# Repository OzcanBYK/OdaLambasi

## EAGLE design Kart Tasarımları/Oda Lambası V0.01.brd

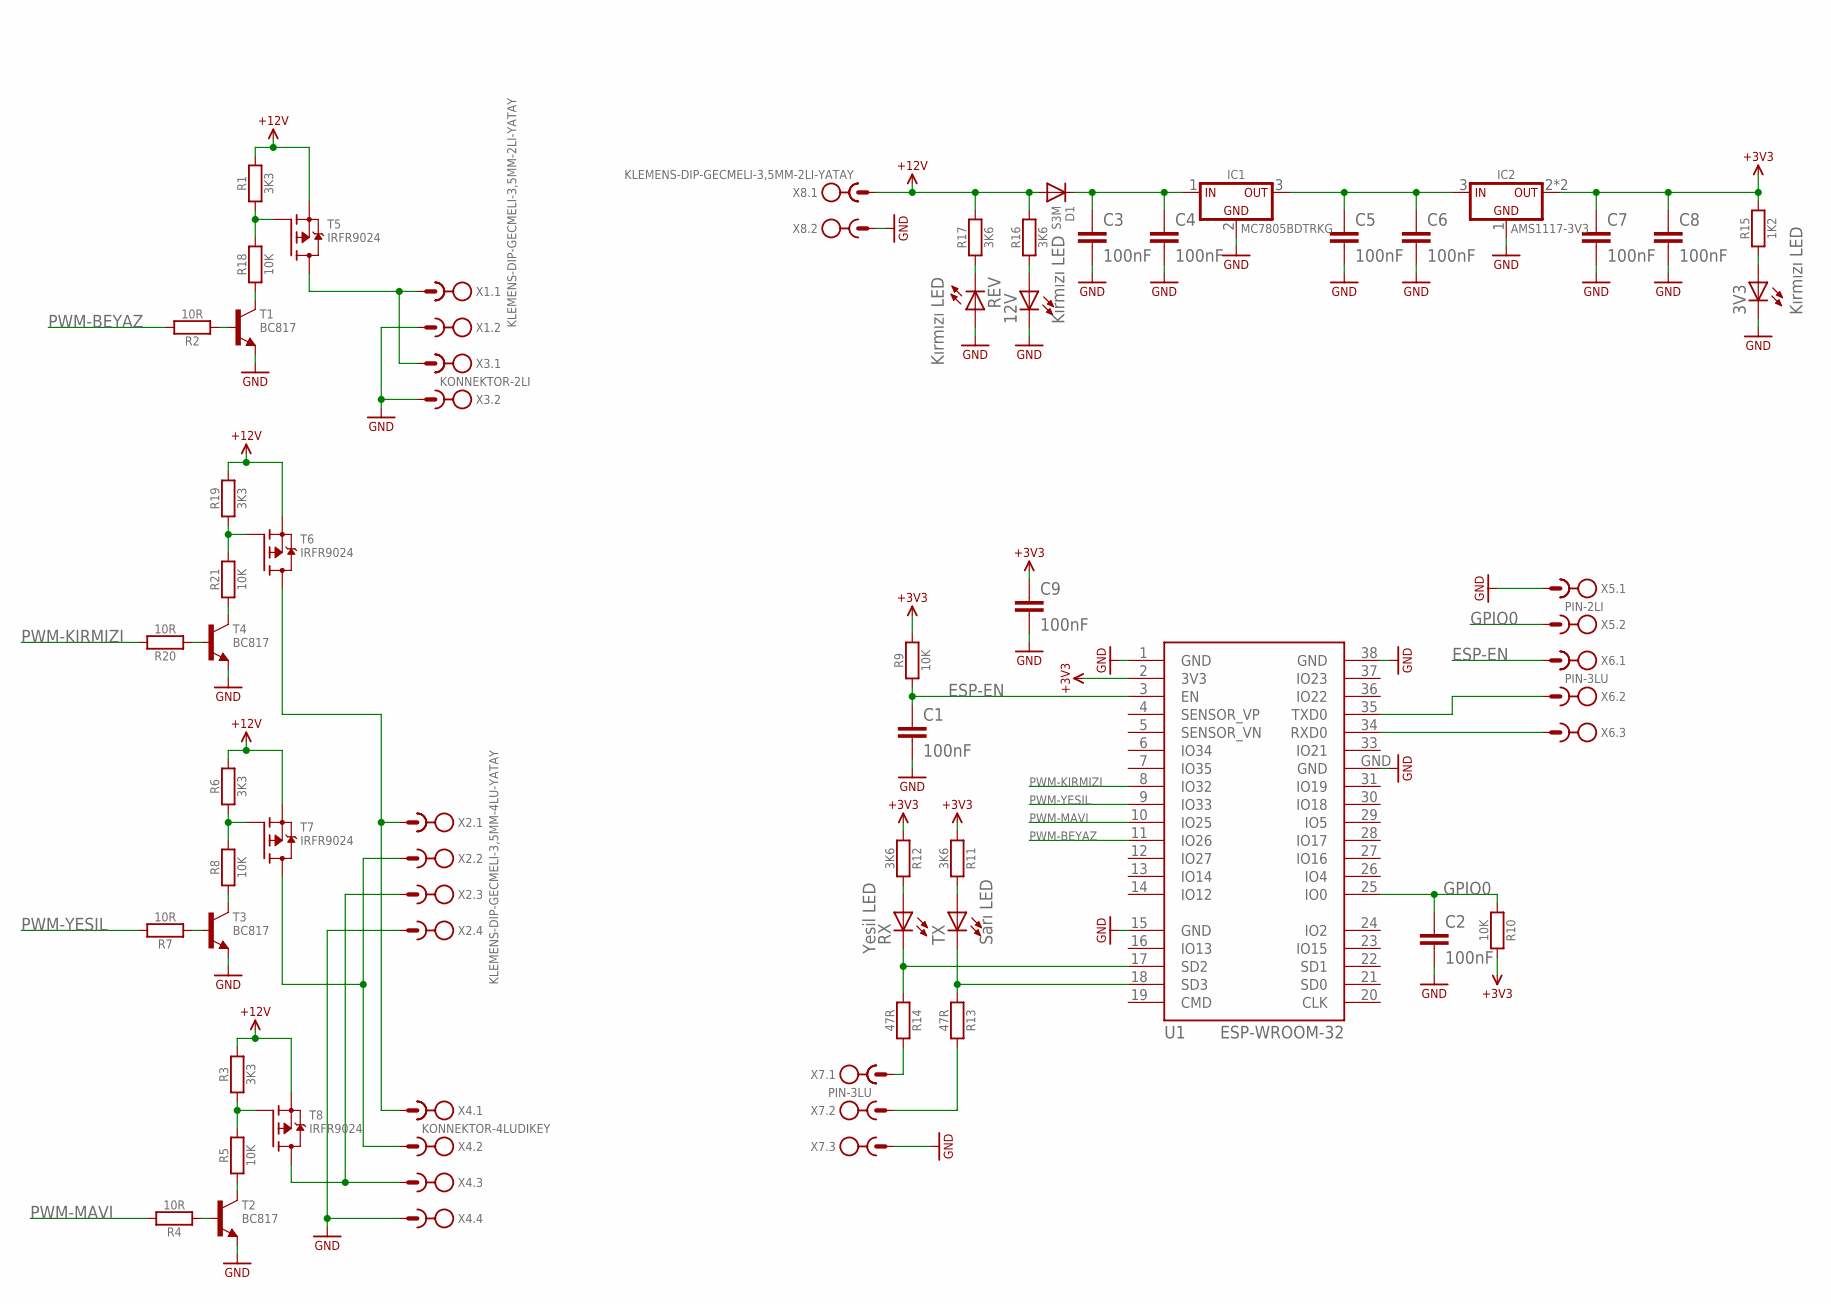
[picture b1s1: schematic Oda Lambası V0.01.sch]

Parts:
3V3, 12V: Kırmızı LED; 0805
C1, C2, C3, C4, C5, C6, C7, C8, C9: 100nF; C1206
D1: S3M; SMC
IC1: MC7805BDTRKG; DPAK
IC2: AMS1117-3V3; SOT223
R1, R3, R6, R19: 3K3; R1206
R2, R4, R7, R20: 10R; R1206
R5, R8, R9, R10, R18, R21: 10K; R1206
R11, R12, R16, R17: 3K6; R1206
R13, R14: 47R; R1206
R15: 1K2; R1206
REV: Kırmızı LED; 0805
RX: Yesil LED; 0805
T1, T2, T3, T4: BC817; SOT23
T5, T6, T7, T8: IRFR9024; DPAK
TX: Sarı LED; 0805
U1: ESP-WROOM-32
X1, X8: KLEMENS-DIP-GECMELI-3,5MM-2LI-YATAY
X2: KLEMENS-DIP-GECMELI-3,5MM-4LU-YATAY
X3: KONNEKTOR-2LI; MOLEX-DIP-2LI-YATAY
X4: KONNEKTOR-4LUDIKEY; MOLEX-DIP-4LU-DIKEY
X5: PIN-2LI; PINHEADER-DIP-2-2.54
X6, X7: PIN-3LU; PINHEADER-DIP-3-2.54

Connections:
+3V3: C7.1, C8.1, C9.1, IC2.2 (OUT), IC2.4 (OUT), R9.2, R10.2, R11.2, R12.2, R15.2, U1.2 (3V3)
+12V: D1.A, R1.2, R3.2, R6.2, R16.2, R17.2, R19.2, T5.3 (S), T6.3 (S), T7.3 (S), T8.3 (S), X8.1
ESP-EN: C1.1, R9.1, U1.3 (EN), X6.1
GND: 3V3.C, 12V.C, C1.2, C2.2, C3.2, C4.2, C5.2, C6.2, C7.2, C8.2, C9.2, IC1.2 (GND), IC2.1 (GND), REV.A, T1.2 (E), T2.2 (E), T3.2 (E), T4.2 (E), U1.1 (GND), U1.15 (GND), U1.38 (GND), U1.GND, X1.2, X2.4, X3.2, X4.4, X5.1, X7.3, X8.2
GPIO0: C2.1, R10.1, U1.25 (IO0), X5.2
unnamed: R1.1, R18.2, T5.1 (G)
unnamed: R3.1, R5.2, T8.1 (G)
unnamed: R5.1, T2.3 (C)
unnamed: R4.1, T2.1 (B)
unnamed: T6.2 (D), X2.1, X4.1
unnamed: T8.2 (D), X2.3, X4.3
unnamed: T5.2 (D), X1.1, X3.1
unnamed: U1.35 (TXD0), X6.2
unnamed: U1.34 (RXD0), X6.3
unnamed: R18.1, T1.3 (C)
unnamed: R2.1, T1.1 (B)
unnamed: R6.1, R8.2, T7.1 (G)
unnamed: R8.1, T3.3 (C)
unnamed: R11.1, TX.A
unnamed: R12.1, RX.A
unnamed: C3.1, C4.1, D1.C, IC1.1 (IN)
unnamed: C5.1, C6.1, IC1.3 (OUT), IC2.3 (IN)
unnamed: R14.1, X7.1
unnamed: R13.1, X7.2
unnamed: R13.2, TX.C, U1.18 (SD3)
unnamed: R14.2, RX.C, U1.17 (SD2)
unnamed: 3V3.A, R15.1
unnamed: 12V.A, R16.1
unnamed: R17.1, REV.C
unnamed: R7.1, T3.1 (B)
unnamed: R19.1, R21.2, T6.1 (G)
unnamed: R21.1, T4.3 (C)
unnamed: R20.1, T4.1 (B)
unnamed: T7.2 (D), X2.2, X4.2
PWM-BEYAZ: R2.2, U1.11 (IO26)
PWM-KIRMIZI: R20.2, U1.8 (IO32)
PWM-MAVI: R4.2, U1.10 (IO25)
PWM-YESIL: R7.2, U1.9 (IO33)

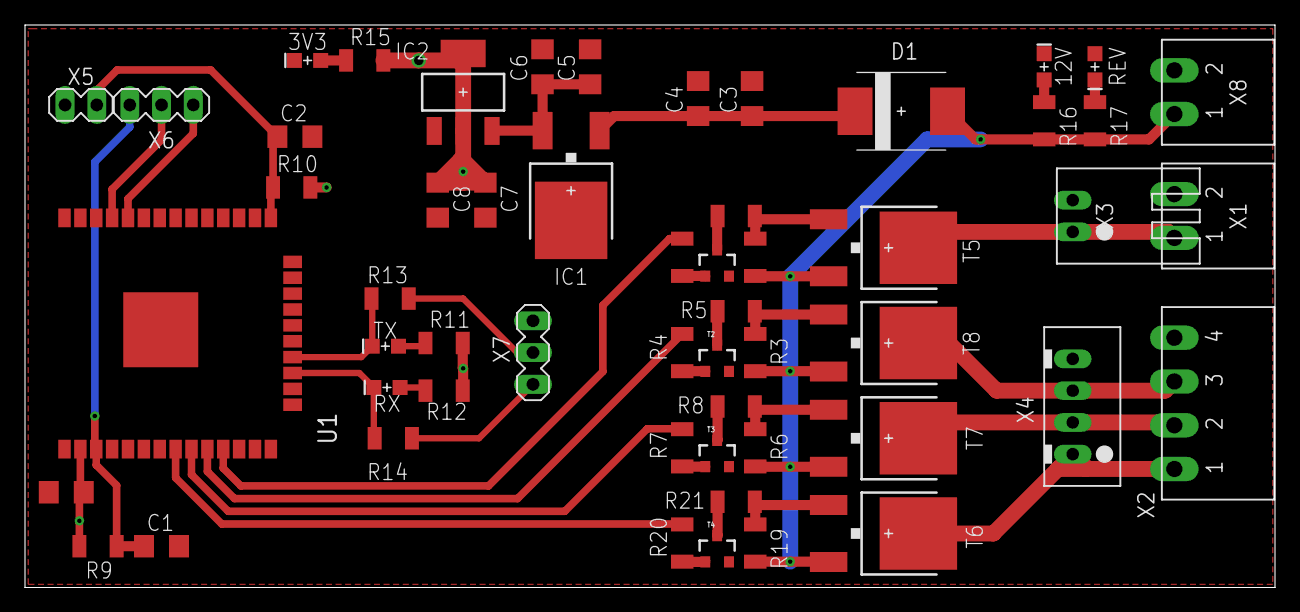
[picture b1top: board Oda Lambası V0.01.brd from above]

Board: 2 copper layers, 100.0 x 45.0 mm, 55 parts (0 on the bottom side), 38 nets.

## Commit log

2023-01-30 Mosfet Testi
    Mosfet Test Etmek için oda lambası projesinin led sürme kısmı yazıldı.
2023-01-30 Kart Tasarımı Eklendi
    Kart tasarımı ve gerber dosyaları eklendi
2023-02-04 Mekanik Tasarım
    Lambanın 3 boyutlu tasarımı eklenmiştir
2023-02-25 First Release
    First Release
2023-02-25 README Düzenlendi

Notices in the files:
parts and their libraries:
Ozcan-ESP32: Creative Commons Attribution-ShareAlike 4.0 International
